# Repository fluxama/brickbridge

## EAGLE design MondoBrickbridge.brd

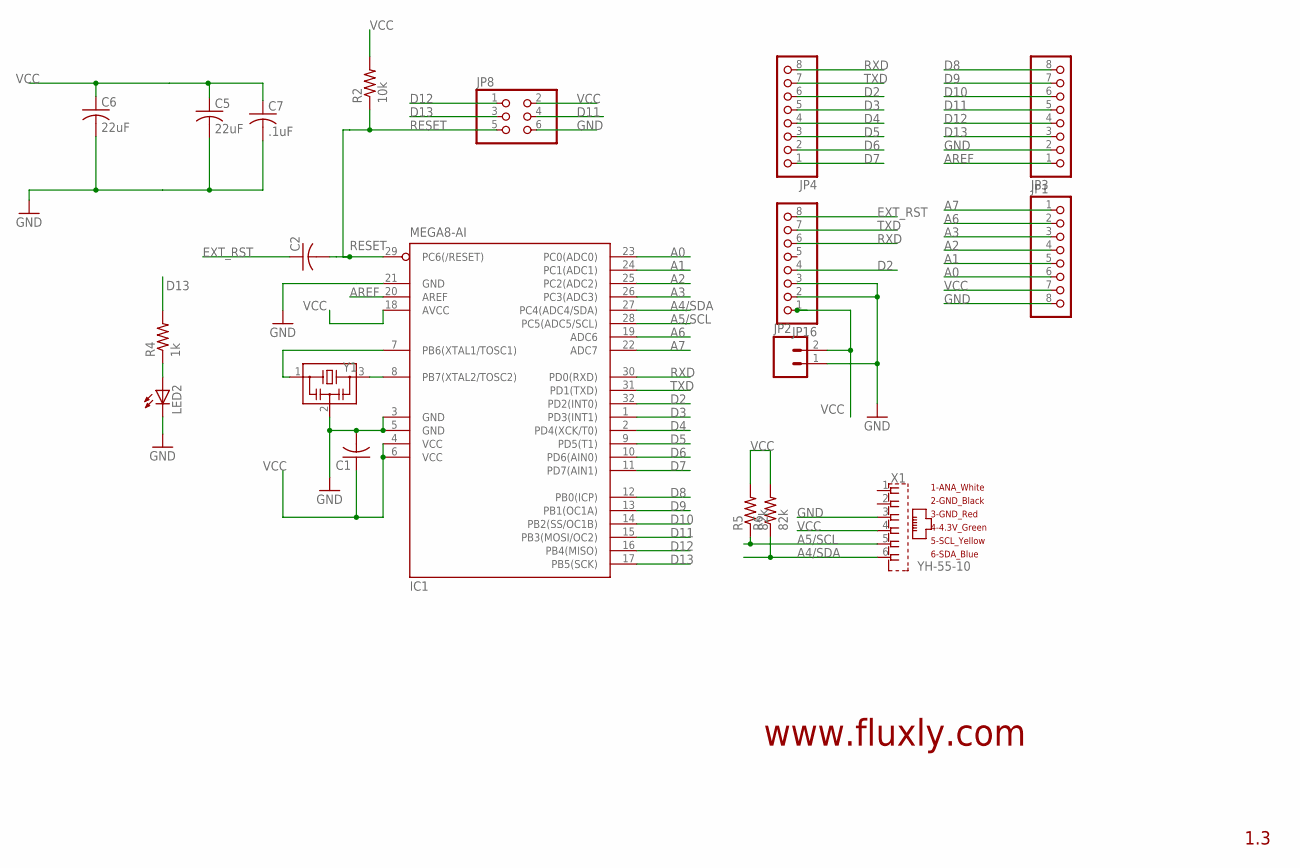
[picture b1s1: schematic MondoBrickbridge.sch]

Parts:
C1, C2: C-USC0805K; C0805K
C5, C6: 22uF; C1206K
C7: .1uF; C0805K
IC1: MEGA8-AI; TQFP32-08
JP1, JP3, JP4, JP16: PINHD-1X8BIG; 1X08-BIG
JP2: M02PTH; 1X02
JP8: PINHD-2X3; 2X03
LED2: LEDCHIPLED_1206; CHIPLED_1206
R2: 10k; M0805
R4: 1k; M0805
R5, R6: 82k; M0805
X1: YH-55-10
Y1: RESONATOR; EFOBM

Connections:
A0: IC1.23 (PC0(ADC0)), JP1.6
A1: IC1.24 (PC1(ADC1)), JP1.5
A2: IC1.25 (PC2(ADC2)), JP1.4
A3: IC1.26 (PC3(ADC3)), JP1.3
A4/SDA: IC1.27 (PC4(ADC4/SDA)), R6.1, X1.6 (6_SDA_BLUE)
A5/SCL: IC1.28 (PC5(ADC5/SCL)), R5.1, X1.5 (5_SCL_YELLOW)
A6: IC1.19 (ADC6), JP1.2
A7: IC1.22 (ADC7), JP1.1
AREF: IC1.20 (AREF), JP3.1
D2: IC1.32 (PD2(INT0)), JP4.6, JP16.4
D3: IC1.1 (PD3(INT1)), JP4.5
D4: IC1.2 (PD4(XCK/T0)), JP4.4
D5: IC1.9 (PD5(T1)), JP4.3
D6: IC1.10 (PD6(AIN0)), JP4.2
D7: IC1.11 (PD7(AIN1)), JP4.1
D8: IC1.12 (PB0(ICP)), JP3.8
D9: IC1.13 (PB1(OC1A)), JP3.7
D10: IC1.14 (PB2(SS/OC1B)), JP3.6
D11: IC1.15 (PB3(MOSI/OC2)), JP3.5, JP8.4
D12: IC1.16 (PB4(MISO)), JP3.4, JP8.1
D13: IC1.17 (PB5(SCK)), JP3.3, JP8.3, R4.2
EXT_RST: C2.1, JP16.8
GND: C1.2, C5.2, C6.2, C7.2, IC1.3 (GND), IC1.5 (GND), IC1.21 (GND), JP1.8, JP2.1, JP3.2, JP8.6, JP16.2, JP16.3, LED2.C, X1.3 (3_GND_RED), Y1.2
unnamed: LED2.A, R4.1
unnamed: IC1.8 (PB7(XTAL2/TOSC2)), Y1.3
unnamed: IC1.7 (PB6(XTAL1/TOSC1)), Y1.1
RESET: C2.2, IC1.29 (PC6(/RESET)), JP8.5, R2.1
RXD: IC1.30 (PD0(RXD)), JP4.8, JP16.6
TXD: IC1.31 (PD1(TXD)), JP4.7, JP16.7
VCC: C1.1, C5.1, C6.1, C7.1, IC1.4 (VCC), IC1.6 (VCC), IC1.18 (AVCC), JP1.7, JP2.2, JP8.2, JP16.1, R2.2, R5.2, R6.2, X1.4 (4_4.3V_GREEN)

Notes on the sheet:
1.3
www.fluxly.com

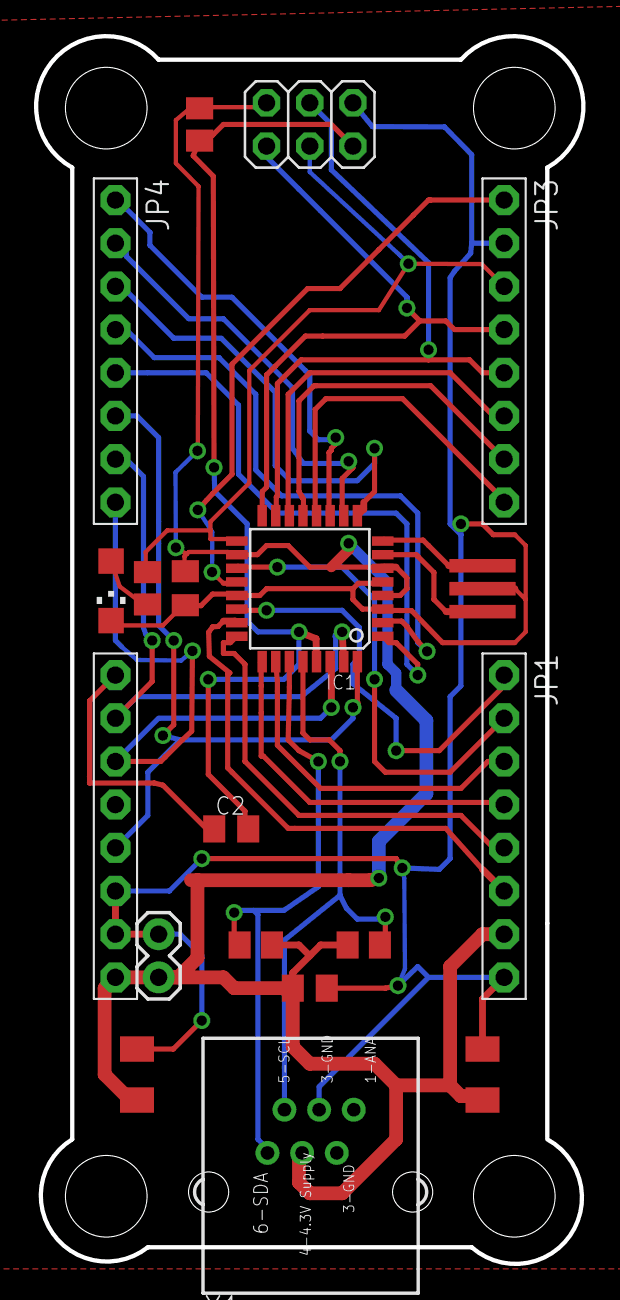
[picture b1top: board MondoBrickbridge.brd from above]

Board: 2 copper layers, 32.2 x 72.2 mm, 19 parts (0 on the bottom side), 30 nets.

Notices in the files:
parts and their libraries:
SparkFun-Connectors: Licensing: CC v3.0 Share-Alike You are welcome to use this library for commercial purposes.
